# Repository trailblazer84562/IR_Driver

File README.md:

# IR_Driver

<!-- Designed by Allen Peters

There are two design in here

The Emitter V2 is a dual IR driver
If I recall, the simulation and part selection is targetting ~0.9A
Works with 2S lipo, 6AA or 6NiMh batteries and performance should be voltage independent

The 360 IR TX and RX design is based off the Emitter V2
It targets a lower current (~200mA?) and drives 8 TSAL 7400 LEDs in a 360 degree pattern
It also has 4 IR receivers, also for a 360 degree pickup pattern -->

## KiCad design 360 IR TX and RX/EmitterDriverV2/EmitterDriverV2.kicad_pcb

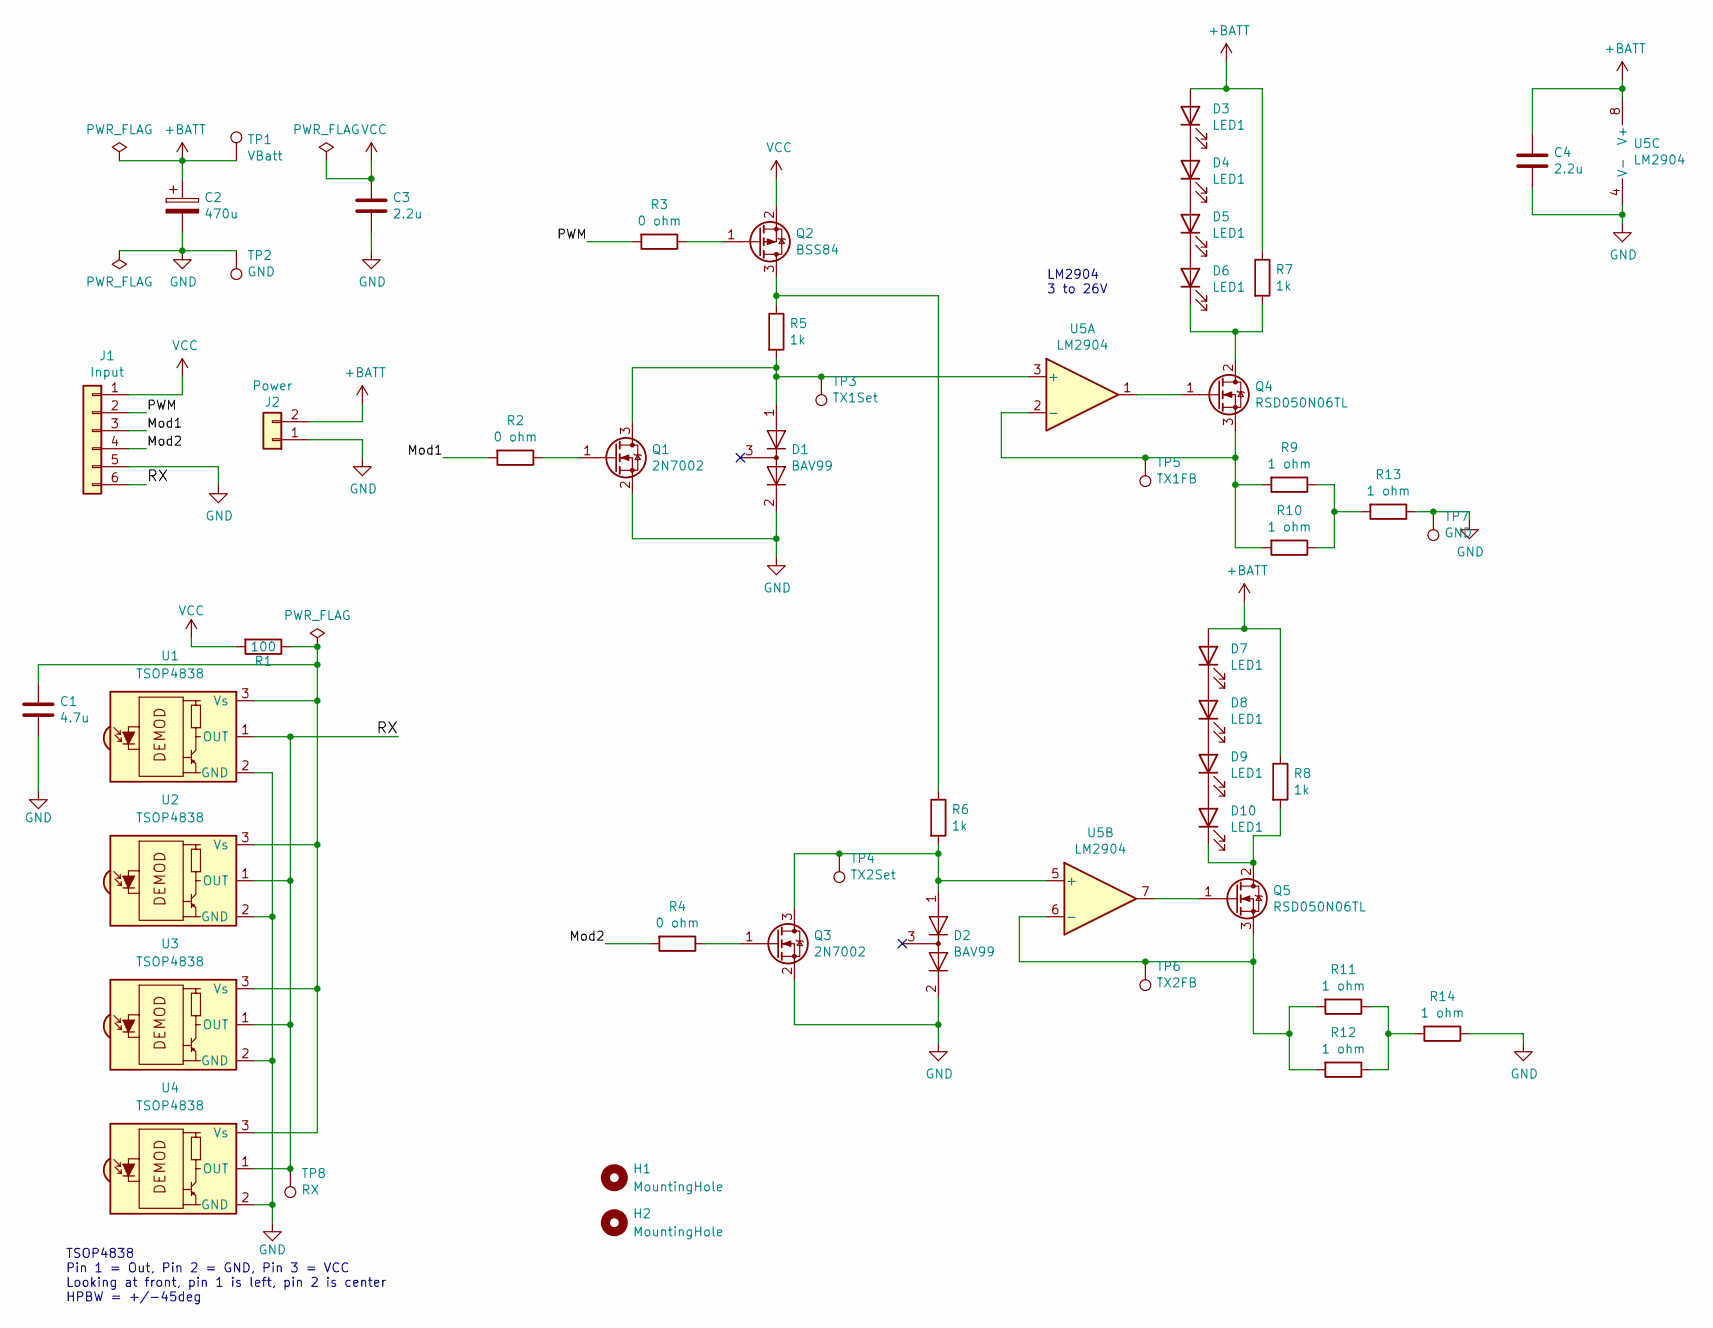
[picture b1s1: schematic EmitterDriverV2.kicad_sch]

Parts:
C1: 4.7u; C_0805_2012Metric
C2: 470u; CP_Radial_D8.0mm_P3.50mm
C3, C4: 2.2u; C_0402
D1, D2: BAV99; SOT-23
D3, D4, D5, D6, D7, D8, D9, D10: LED1; LED_D5.0mm
H1, H2: MountingHole; MountingHole_3.2mm_M3
J1: Input; Hirose_DF13-06P-1.25DSA_06x1.25mm_Straight
J2: Power; JST_XH_B02B-XH-A_02x2.50mm_Straight
Q1, Q3: 2N7002; SOT-23
Q2: BSS84; SOT-23
Q4, Q5: RSD050N06TL; TO-252-2
R1: 100; R_0805_2012Metric
R2, R3, R4: 0 ohm; R_0805
R5, R6, R7, R8: 1k; R_0805
R9, R10, R11, R12, R13, R14: 1 ohm; R_0805_2012Metric
TP1: VBatt; TestPoint_Keystone_5000-5004_Miniature
TP2, TP7: GND; TestPoint_Keystone_5000-5004_Miniature
TP3: TX1Set; TestPoint_Keystone_5000-5004_Miniature
TP4: TX2Set; TestPoint_Keystone_5000-5004_Miniature
TP5: TX1FB; TestPoint_Keystone_5000-5004_Miniature
TP6: TX2FB; TestPoint_Keystone_5000-5004_Miniature
TP8: RX; TestPoint_Keystone_5000-5004_Miniature
U1, U2, U3, U4: TSOP4838; Vishay_MOLD-3Pin
U5: LM2904; SOIC-8_3.9x4.9mm_Pitch1.27mm

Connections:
+BATT: C2.1, C4.1, D3.2 (A), D7.2 (A), J2.2, R7.1, R8.1, TP1.1, U5.8 (V+)
/Mod1: J1.3, R2.2
/Mod2: J1.4, R4.2
/PWM: J1.2, R3.2
/RX: J1.6, TP8.1, U1.1 (OUT), U2.1 (OUT), U3.1 (OUT), U4.1 (OUT)
GND: C1.2, C2.2, C3.2, C4.2, D1.2 (A), D2.2 (A), J1.5, J2.1, Q1.2 (S), Q3.2 (S), R13.1, R14.1, TP2.1, TP7.1, U1.2 (GND), U2.2 (GND), U3.2 (GND), U4.2 (GND), U5.4 (V-)
unnamed: C1.1, R1.1, U1.3 (Vs), U2.3 (Vs), U3.3 (Vs), U4.3 (Vs)
unnamed: D1.1 (K), Q1.3 (D), R5.2, TP3.1, U5.3 (+)
unnamed: D2.1 (K), Q3.3 (D), R6.2, TP4.1, U5.5 (+)
unnamed: D3.1 (K), D4.2 (A)
unnamed: D4.1 (K), D5.2 (A)
unnamed: D5.1 (K), D6.2 (A)
unnamed: D6.1 (K), Q4.2 (D), R7.2
unnamed: D7.1 (K), D8.2 (A)
unnamed: D8.1 (K), D9.2 (A)
unnamed: D10.1 (K), Q5.2 (D), R8.2
unnamed: D9.1 (K), D10.2 (A)
unnamed: Q1.1 (G), R2.1
unnamed: Q2.1 (G), R3.1
unnamed: Q2.3 (D), R5.1, R6.1
unnamed: Q3.1 (G), R4.1
unnamed: Q4.1 (G), U5.1
unnamed: Q4.3 (S), R9.2, R10.2, TP5.1, U5.2 (-)
unnamed: Q5.1 (G), U5.7
unnamed: Q5.3 (S), R11.2, R12.2, TP6.1, U5.6 (-)
unnamed: R9.1, R10.1, R13.2
unnamed: R11.1, R12.1, R14.2
VCC: C3.1, J1.1, Q2.2 (S), R1.2

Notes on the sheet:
TSOP4838 Pin 1 = Out, Pin 2 = GND, Pin 3 = VCC Looking at front, pin 1 is left, pin 2 is center HPBW = +/-45deg
LM2904 3 to 26V

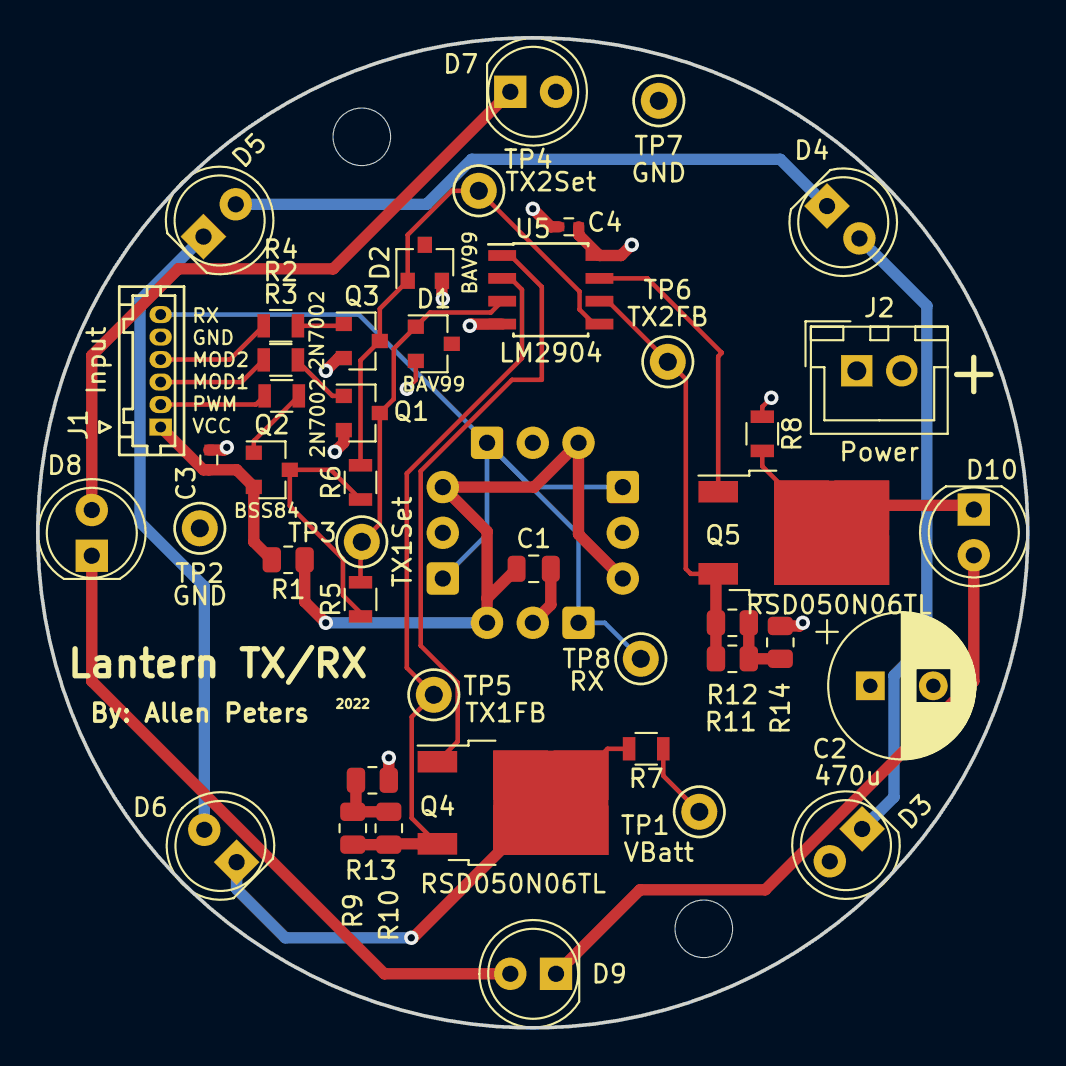
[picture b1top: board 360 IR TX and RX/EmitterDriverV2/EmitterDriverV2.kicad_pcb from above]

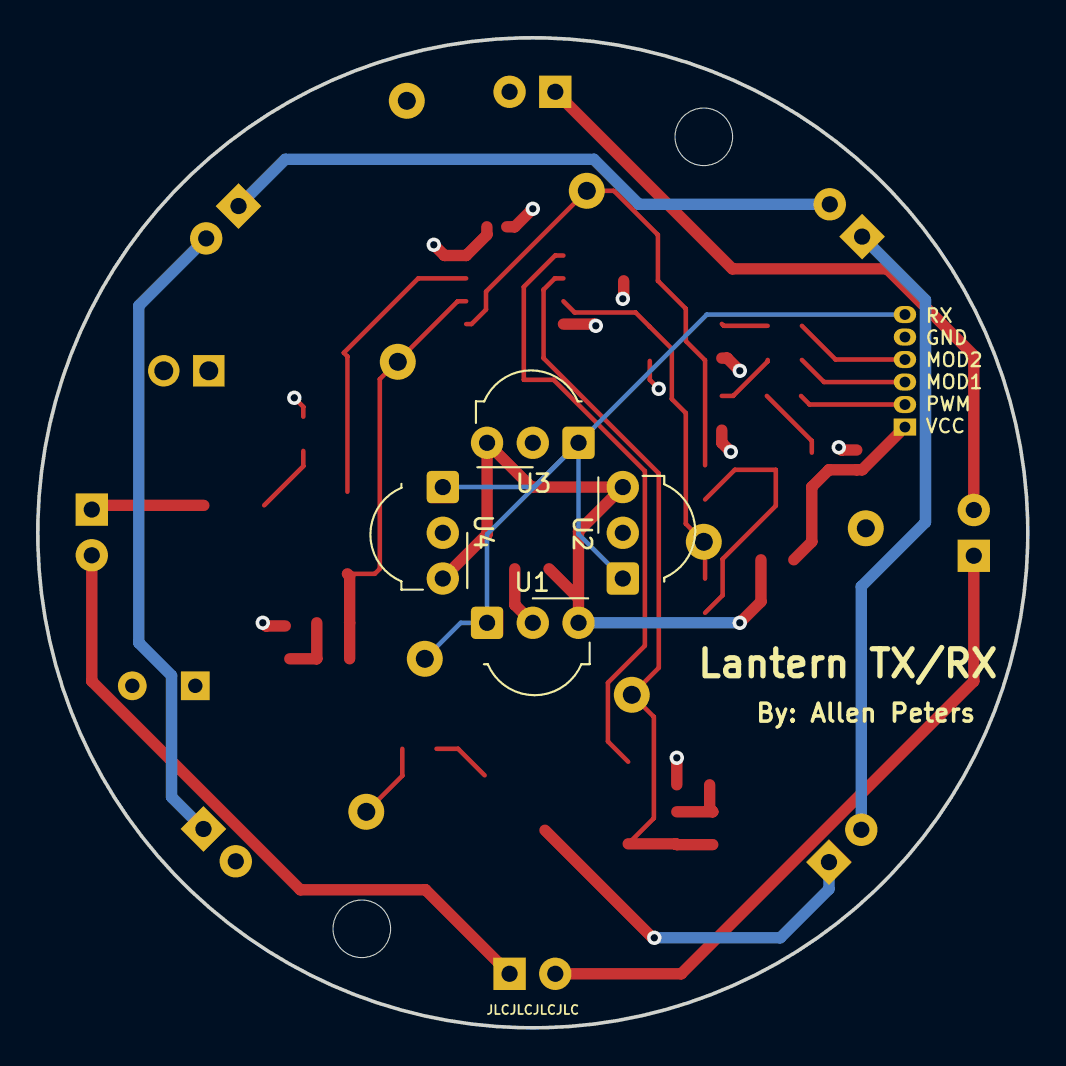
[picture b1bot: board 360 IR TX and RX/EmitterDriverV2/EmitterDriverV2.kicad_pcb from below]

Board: 4 copper layers, 55.0 x 55.0 mm, 50 parts (4 on the bottom side), 28 nets.

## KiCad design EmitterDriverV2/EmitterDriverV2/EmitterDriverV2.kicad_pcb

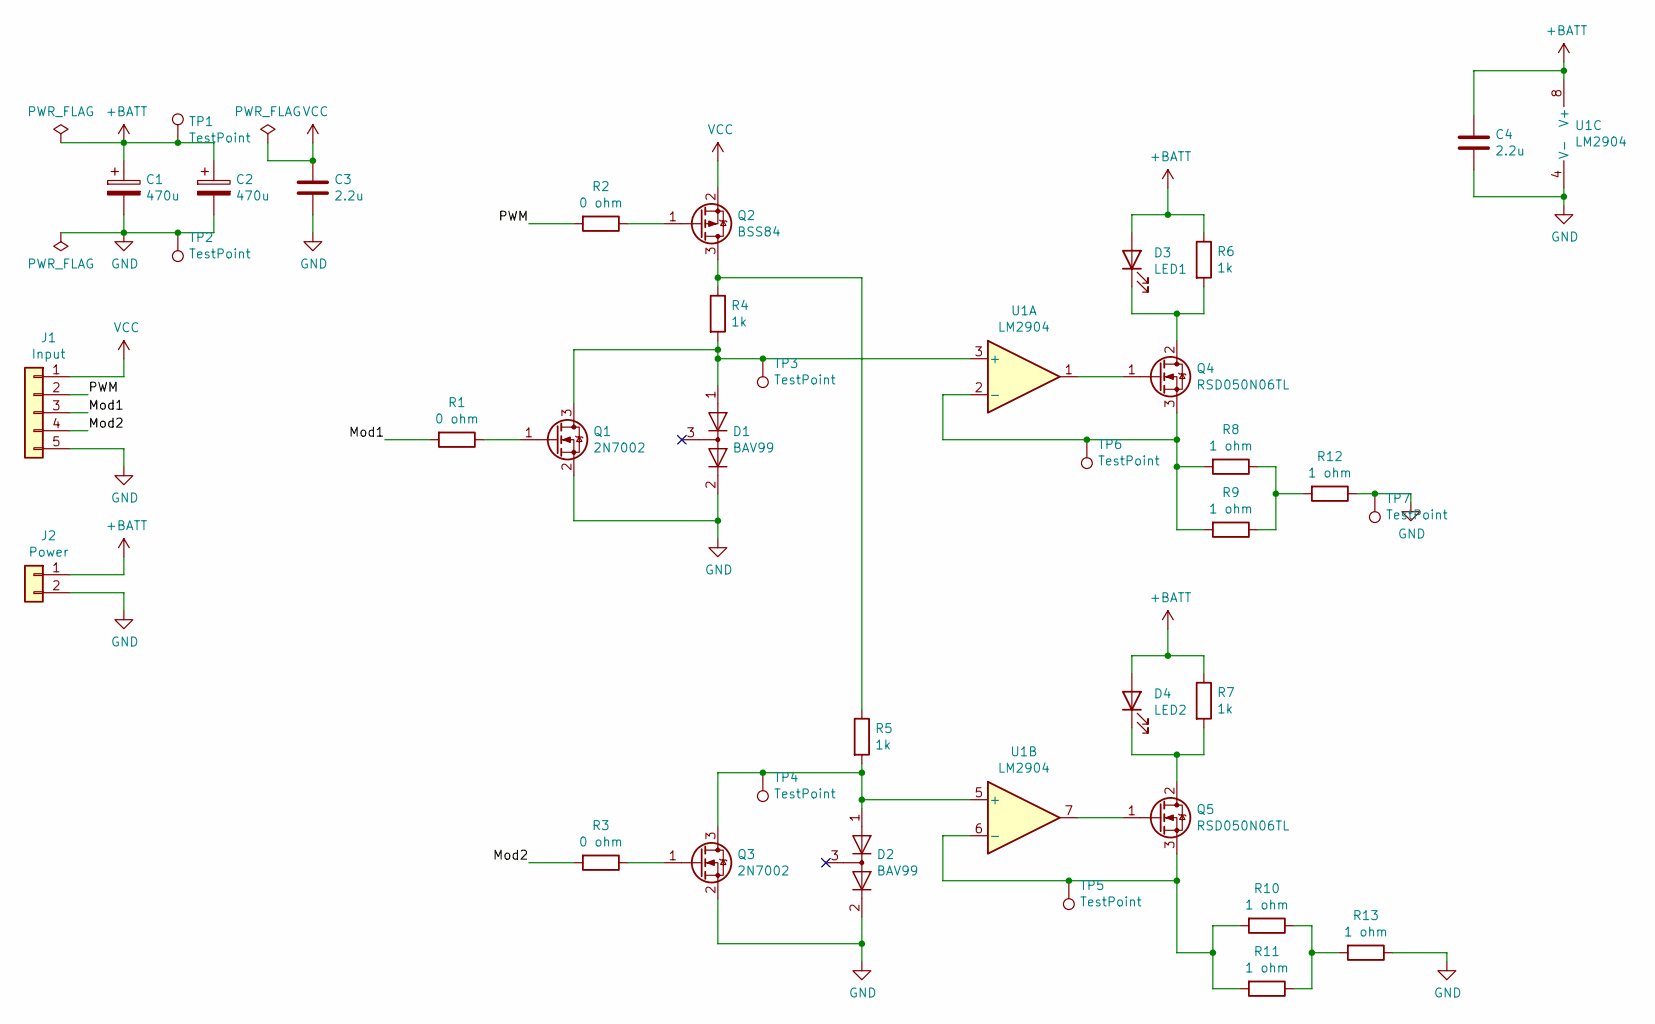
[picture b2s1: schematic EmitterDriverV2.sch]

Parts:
C1, C2: 470u; CP_Radial_D8.0mm_P3.50mm
C3, C4: 2.2u; C_0402
D1, D2: BAV99; SOT-23
D3: LED1; JST_XH_B02B-XH-A_02x2.50mm_Straight
D4: LED2; JST_XH_B02B-XH-A_02x2.50mm_Straight
J1: Input; Hirose_DF13-06P-1.25DSA_06x1.25mm_Straight
J2: Power; JST_XH_B02B-XH-A_02x2.50mm_Straight
Q1, Q3: 2N7002; SOT-23
Q2: BSS84; SOT-23
Q4, Q5: RSD050N06TL; TO-252-2
R1, R2, R3: 0 ohm; R_0805
R4, R5, R6, R7: 1k; R_0805
R8, R9, R10, R11, R12, R13: 1 ohm; R_Axial_DIN0414_L11.9mm_D4.5mm_P5.08mm_Vertical
TP1, TP2, TP3, TP4, TP5, TP6, TP7: TestPoint; Test_Point_Keystone_5000-5004_Miniature
U1: LM2904; SOIC-8_3.9x4.9mm_Pitch1.27mm

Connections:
+BATT: C1.1, C2.1, C4.1, D3.2 (A), D4.2 (A), J2.1, R6.1, R7.1, TP1.1, U1.8 (V+); also elsewhere on the board
/Mod1: J1.3, R1.2
/Mod2: J1.4, R3.2
/PWM: J1.2, R2.2
GND: C1.2, C2.2, C3.2, C4.2, D1.2 (A), D2.2 (A), J1.5, J2.2, Q1.2 (S), Q3.2 (S), R12.1, R13.1, TP2.1, TP7.1, U1.4 (V-); also elsewhere on the board
unnamed: D1.1 (K), Q1.3 (D), R4.2, TP3.1, U1.3 (+)
unnamed: D2.1 (K), Q3.3 (D), R5.2, TP4.1, U1.5 (+)
unnamed: D3.1 (K), Q4.2 (D), R6.2
unnamed: D4.1 (K), Q5.2 (D), R7.2
unnamed: Q1.1 (G), R1.1
unnamed: Q2.1 (G), R2.1
unnamed: Q2.3 (D), R4.1, R5.1
unnamed: Q3.1 (G), R3.1
unnamed: Q4.1 (G), U1.1
unnamed: Q4.3 (S), R8.2, R9.2, TP6.1, U1.2 (-)
unnamed: Q5.1 (G), U1.7
unnamed: Q5.3 (S), R10.2, R11.2, TP5.1, U1.6 (-)
unnamed: R10.1, R11.1, R13.2
unnamed: R8.1, R9.1, R12.2
VCC: C3.1, J1.1, Q2.2 (S)

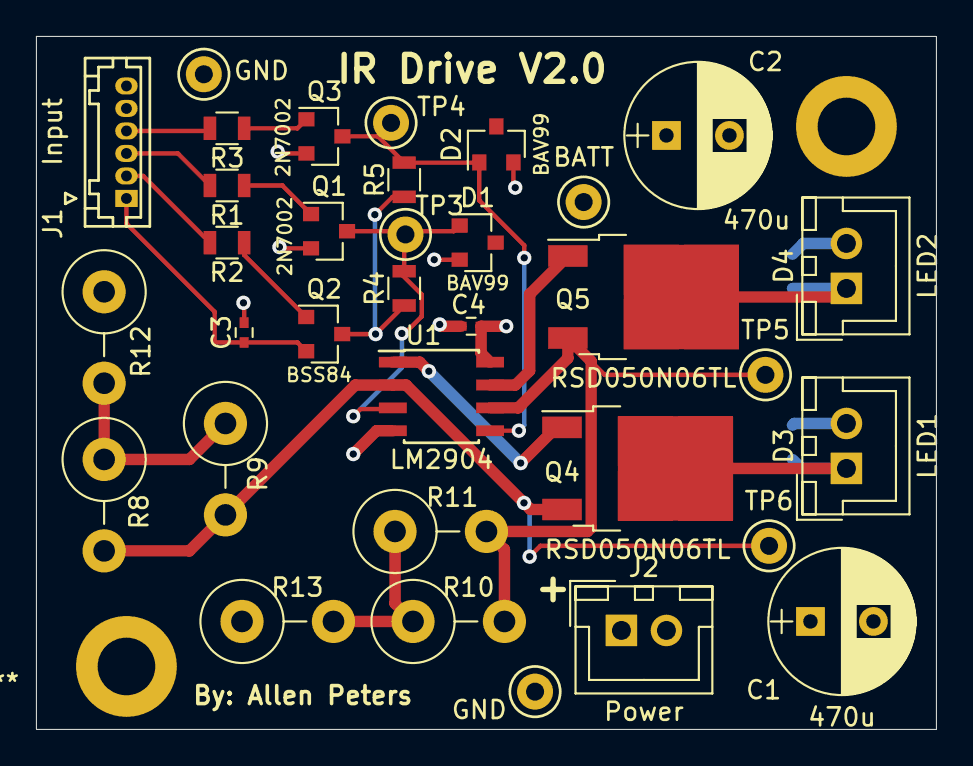
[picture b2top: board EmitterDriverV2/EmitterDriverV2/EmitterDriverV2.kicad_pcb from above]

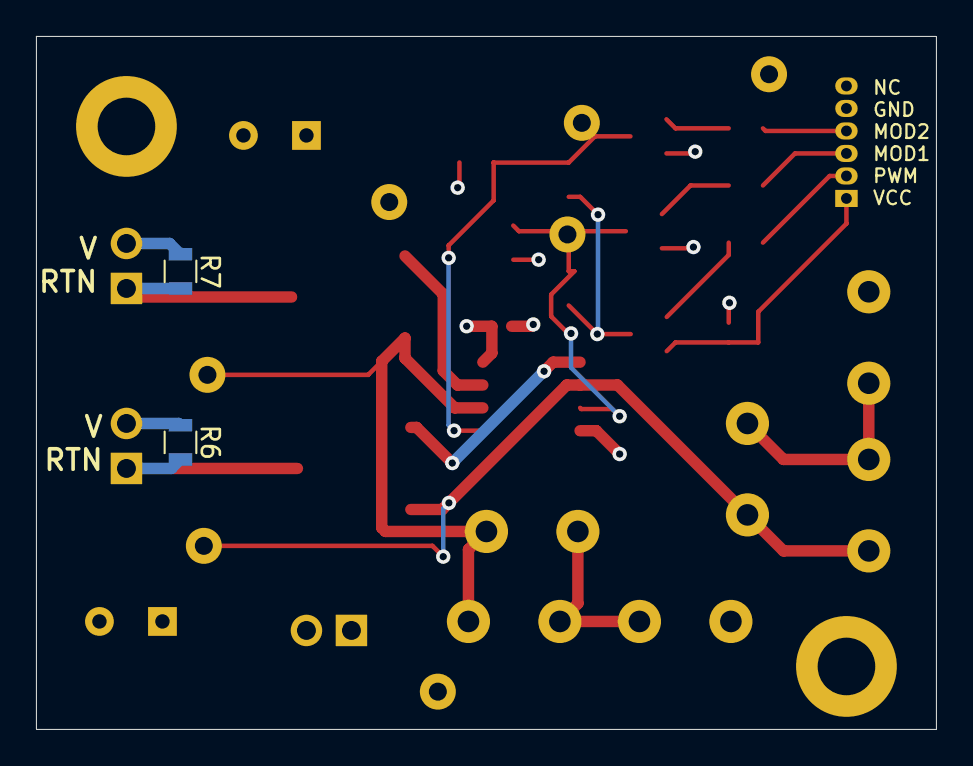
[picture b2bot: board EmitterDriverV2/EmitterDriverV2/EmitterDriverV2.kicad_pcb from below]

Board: 4 copper layers, 50.0 x 38.5 mm, 36 parts (2 on the bottom side), 20 nets.

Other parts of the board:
BATT: TestPoint; Test_Point_Keystone_5000-5004_Miniature
GND: TestPoint; Test_Point_Keystone_5000-5004_Miniature
GND#2: TestPoint; Test_Point_Keystone_5000-5004_Miniature

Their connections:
+BATT: BATT.1; also elsewhere on the board
GND: GND.1, GND#2.1; also elsewhere on the board

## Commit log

2023-11-03 Initial Upload of Designs
